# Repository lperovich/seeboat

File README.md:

# SeeBoat

Laura Perovich (perovich@media.mit.edu, Object-based Media, MIT Media Lab)

This project includes the code, hardware, and fabrication guides for SeeBoat, a community centered waterbody monitoring and data display platform. 

SeeBoat is a fleet of remote controlled boats that measure and display water quality in real time. It allows communities to explore water quality in their local lakes, rivers, and streams by changing the color of the boat in response to changes to the water quality. This data physicalization contextualizes the information and makes the water pollution data present in people's daily lives.

The boats measure water temperature, conductivity, and turbidity and display the data by real-time changes to the colors of the LEDs on the boat. Numeric sensor data is also transmitted via radio, visible through an Android app, and can be further recording using long exposure photos. SeeBoat makes environmental data experiential and interactive to help both communities and researchers better understand pollution and its implications.

The system is based on the Adafruit Feather M0 with RFM95 LoRa Radio (900MHz).

See "hardware" for a parts list, sensor schematics and board files, and 3D print files for sensors attachments.

See "software" for Arduino code for the entire system (main) and for each of the sensors (testing)

See "tutorials" for sensor fabrication guides and testing recommendations.

With technical contributions from Don Blair, Robert Henning, Sophia Struckman, Rod Bayliss, Rima Rebei, and Talia Spitz. Additional testing and assistance by ECO youth group (GreenRoots), Katherine Paseman, Claudia Chen, and Brian Mayton. 

Thanks to contributors Sara Wylie (Northeastern University) and Roseann Bongiovanni (GreenRoots). 

With funding and support from the Object Based Media (V. Michael Bove), the Media Lab Elements Fellows, and the Council for the Arts at MIT.

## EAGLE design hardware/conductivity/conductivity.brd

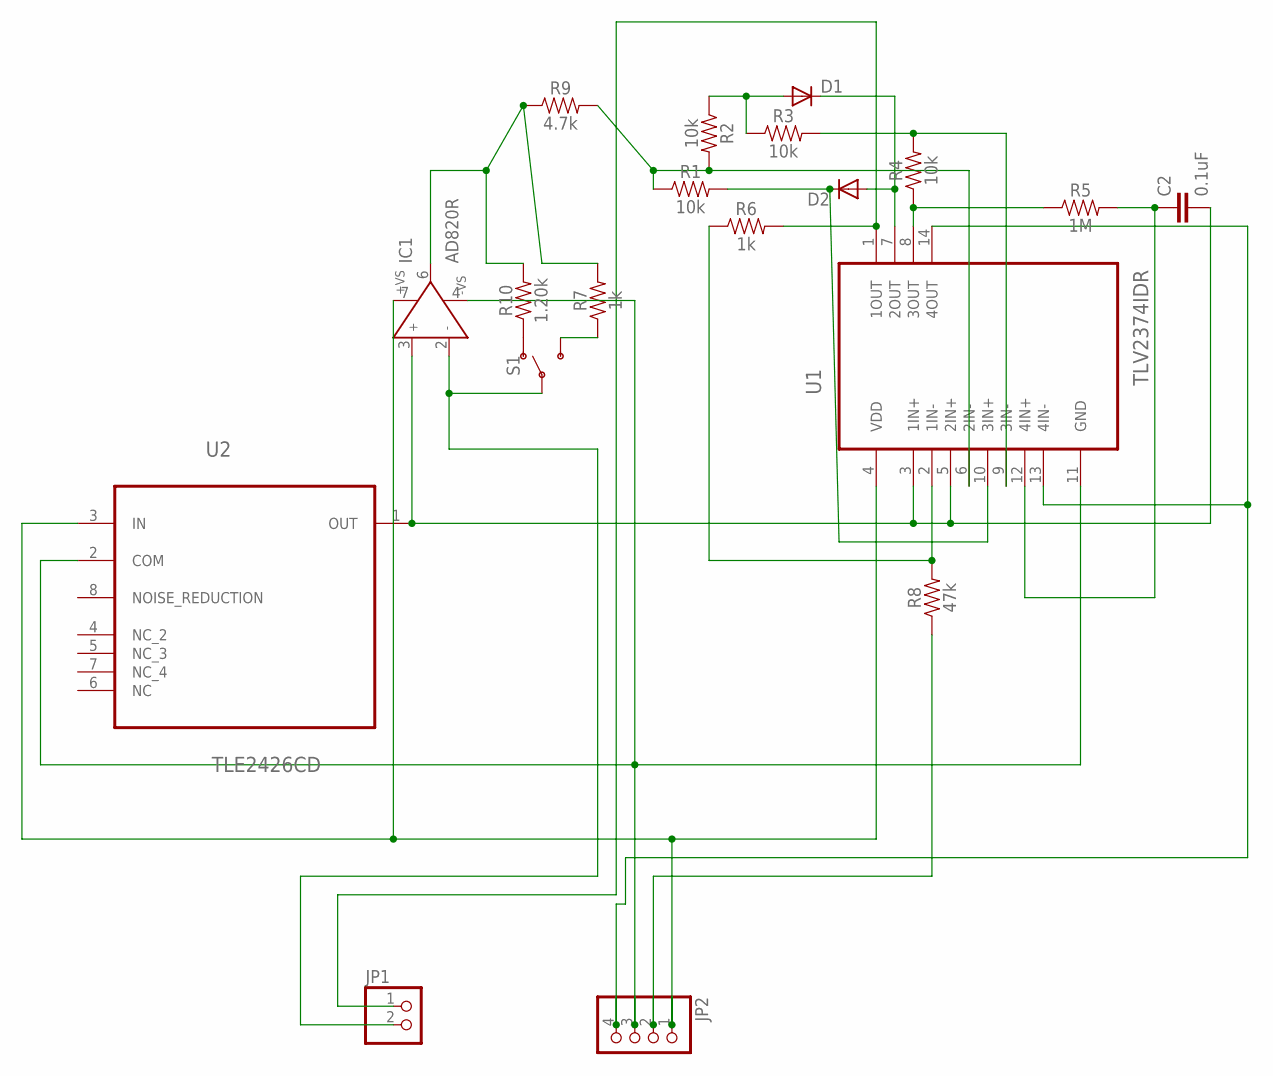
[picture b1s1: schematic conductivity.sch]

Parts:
C2: 0.1uF; 0603
D1, D2: DIODESOD123; SOD123
IC1: AD820R; SO8
JP1: PINHD-1X2; 1X02
JP2: PINHD-1X4; 1X04
R1, R2, R3, R4: 10k; 0603
R5: 1M; 0603
R6, R7: 1k; 0603
R8: 47k; 0603
R9: 4.7k; 0603
R10: 1.20k; 0603
S1: SWITCH-SPDT-SMD-AYZ0202; SWITCH_DPDT_SMD_AYZ0202
U1: TLV2374IDR; SOIC127P600X175-14N
U2: TLE2426CD; SOIC127P600X175-8N

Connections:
FROMWATER: IC1.2 (IN-), JP1.2, S1.2
unnamed: IC1.7 (+VS), JP2.1, U1.4 (VDD), U2.3 (IN)
unnamed: R10.1, S1.1 (O)
unnamed: C2.2, IC1.3 (IN+), U1.3 (1IN+), U1.5 (2IN+), U2.1 (OUT)
unnamed: R6.1, R8.2, U1.2 (1IN-)
unnamed: IC1.6 (OUT), R7.2, R9.1, R10.2
unnamed: R1.1, R2.2, R9.2, U1.6 (2IN-)
unnamed: D1.ANODE (A), R2.1, R3.1
unnamed: D1.CATHODE (C), D2.ANODE (A), U1.7 (2OUT)
unnamed: D2.CATHODE (C), R1.2, U1.10 (3IN+)
unnamed: R3.2, R4.2, U1.9 (3IN-)
unnamed: R4.1, R5.1, U1.8 (3OUT)
unnamed: C2.1, R5.2, U1.12 (4IN+)
unnamed: JP2.4, U1.13 (4IN-), U1.14 (4OUT)
unnamed: JP2.2, R8.1
unnamed: IC1.4 (-VS), JP2.3, U1.11 (GND), U2.2 (COM)
unnamed: JP1.1, R6.2, U1.1 (1OUT)
unnamed: R7.1, S1.3 (S)

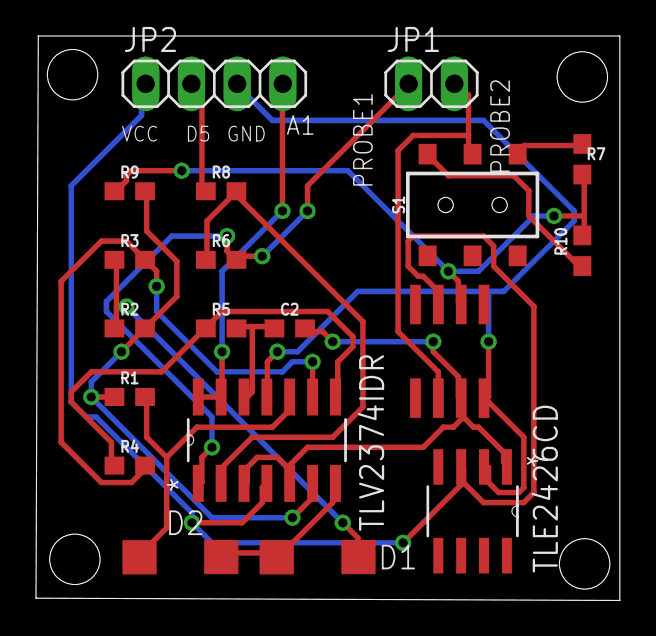
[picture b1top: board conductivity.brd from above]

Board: 2 copper layers, 32.4 x 31.4 mm, 19 parts (0 on the bottom side), 18 nets.

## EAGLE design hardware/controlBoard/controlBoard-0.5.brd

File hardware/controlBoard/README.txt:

Laura Perovich: SeeBoat control board for all the sensors 

--third board layer to be used with Featherwing ultimate GPS and Feather M0 LoRa
--see github parts list in hardware folder for parts details

######### Update 7/3/19
Fixed the labels on the LED strand connector

######### Update 6/23/18
Removed on board LED, spaced out the headers to better fit all the parts and the labels
Included DotStar LED strand connector
Water sensor to tell if it's in water is unnecessary, not implemented

######### Update 5/25/17
Combines the fishet-0.1 board with GPS to works as a breakout board for the feather M0 w/LoRa

parts from the fishnet to include:
*tricolor LED (3 pwm pins, other sides to ground)
*on/off switch for board
*temperature sensor connector (SDA, SCL, GND, PWR)
*turbidity sensor connector
*conductivity sensor connector
*water sensor (to tell if it's in water or not) [UNNECESSARY, NOT IMPLEMENTED]

GPS featherwing includes:
*GPS
*clock via GPS

#############################################
ORIGINAL BOARD LAYOUT:
# Adafruit-Ultimate-GPS-FeatherWing-PCB
PCB files for the Adafruit Ultimate GPS FeatherWing
Format is EagleCAD schematic and board layout
For more details, check out the product page at
   * https://www.adafruit.com/products/3133
Designed by Adafruit Industries.  
Creative Commons Attribution, Share-Alike license, check license.txt for more information
All text above must be included in any redistribution

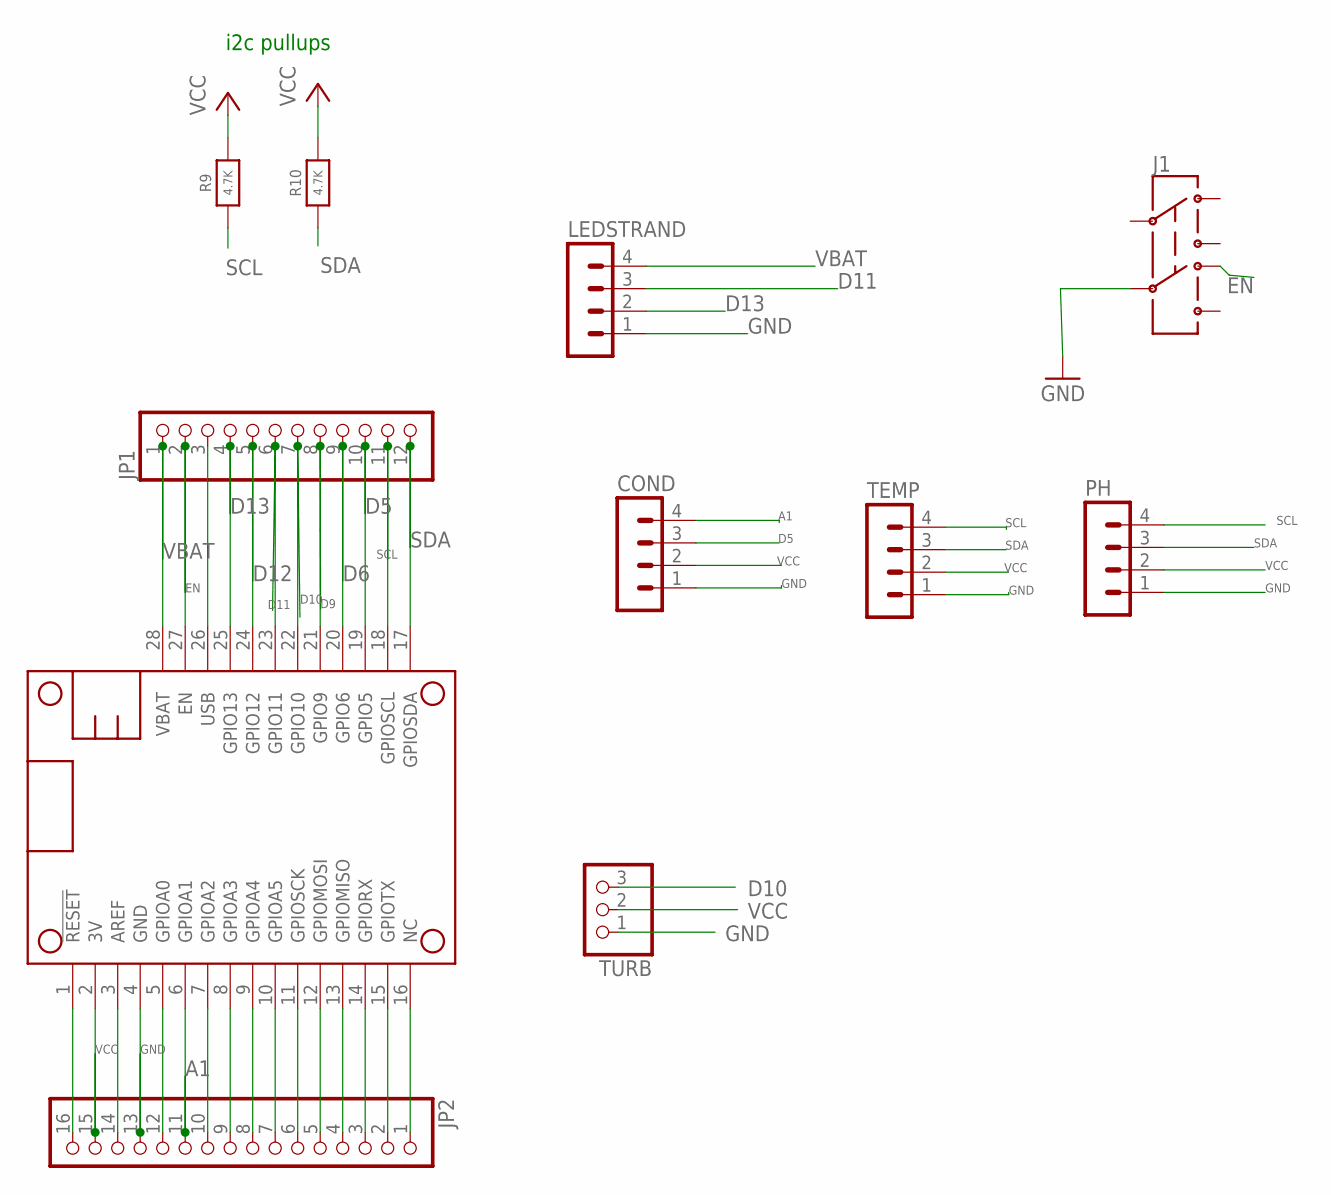
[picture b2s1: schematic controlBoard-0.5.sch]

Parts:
COND: MA04-1
J1: AYZ0202
JP1: PINHD-1X12; 1X12
JP2: PINHD-1X16; 1X16
LEDSTRAND: MA04-1
MS1: FEATHERWING
PH: MA04-1
R9, R10: 4.7K; 0603-NO
TEMP: MA04-1
TURB: PINHD-1X3; 1X03

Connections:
A1: COND.4, JP2.11, MS1.6 (GPIOA1)
D5: COND.3, JP1.10, MS1.19 (GPIO5)
D6: JP1.9, MS1.20 (GPIO6)
D9: JP1.8, MS1.21 (GPIO9)
D10: JP1.7, MS1.22 (GPIO10), TURB.3
D11: JP1.6, LEDSTRAND.3, MS1.23 (GPIO11)
D12: JP1.5, MS1.24 (GPIO12)
D13: JP1.4, LEDSTRAND.2, MS1.25 (GPIO13)
EN: J1.6 (4), JP1.2, MS1.27 (EN)
GND: COND.1, J1.5, JP2.13, LEDSTRAND.1, MS1.4 (GND), PH.1, TEMP.1, TURB.1
unnamed: JP2.1, MS1.16 (NC)
unnamed: JP2.2, MS1.15 (GPIOTX)
unnamed: JP2.3, MS1.14 (GPIORX)
unnamed: JP2.4, MS1.13 (GPIOMISO)
unnamed: JP2.5, MS1.12 (GPIOMOSI)
unnamed: JP2.6, MS1.11 (GPIOSCK)
unnamed: JP2.7, MS1.10 (GPIOA5)
unnamed: JP2.8, MS1.9 (GPIOA4)
unnamed: JP2.9, MS1.8 (GPIOA3)
unnamed: JP2.10, MS1.7 (GPIOA2)
unnamed: JP2.12, MS1.5 (GPIOA0)
unnamed: JP2.14, MS1.3 (AREF)
unnamed: JP2.16, MS1.1 (!RESET)
SCL: JP1.11, MS1.18 (GPIOSCL), PH.4, R9.1, TEMP.4
SDA: JP1.12, MS1.17 (GPIOSDA), PH.3, R10.1, TEMP.3
USB: JP1.3, MS1.26 (USB)
VBAT: JP1.1, LEDSTRAND.4, MS1.28 (VBAT)
VCC: COND.2, JP2.15, MS1.2 (3V), PH.2, R9.2, R10.2, TEMP.2, TURB.2

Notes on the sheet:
i2c pullups

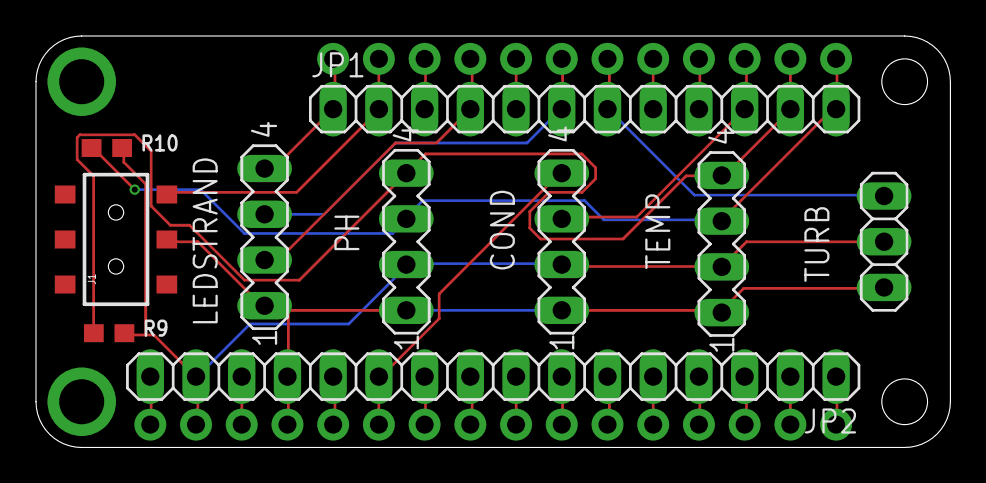
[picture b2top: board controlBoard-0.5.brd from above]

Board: 2 copper layers, 50.8 x 22.9 mm, 11 parts (0 on the bottom side), 28 nets.

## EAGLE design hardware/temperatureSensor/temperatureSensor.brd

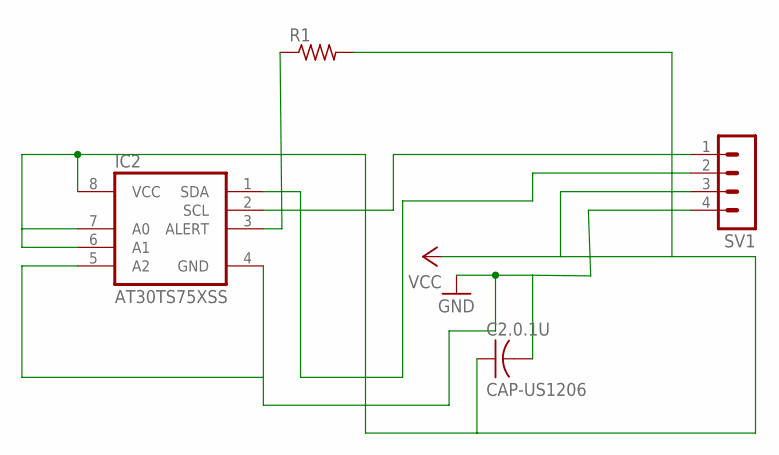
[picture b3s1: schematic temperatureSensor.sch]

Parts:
C2.0.1U: CAP-US1206; C1206
IC2: AT30TS75XSS; SO8
R1: RES-US1206; R1206
SV1: MA04-1

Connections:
D2: IC2.3 (ALERT), R1.1
GND: C2.0.1U.2, IC2.4 (GND), IC2.5 (A2), SV1.4
unnamed: IC2.2 (SCL), SV1.1
SDA: IC2.1 (SDA), SV1.2
VCC: C2.0.1U.1, IC2.6 (A1), IC2.7 (A0), IC2.8 (VCC), R1.2, SV1.3

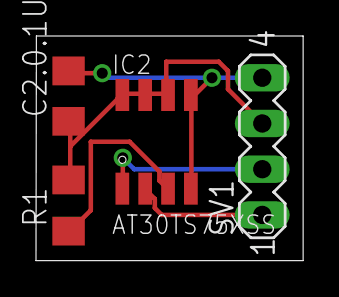
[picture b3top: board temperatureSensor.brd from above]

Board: 2 copper layers, 14.8 x 12.5 mm, 4 parts (0 on the bottom side), 5 nets.

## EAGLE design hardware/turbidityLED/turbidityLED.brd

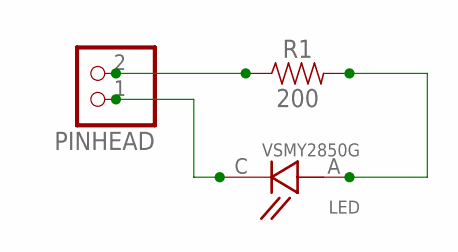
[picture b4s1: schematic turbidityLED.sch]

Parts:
LED: VSMY2850G; SOD4223X279N
PINHEAD: PINHD-1X2; 1X02
R1: 200; 0603

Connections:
unnamed: PINHEAD.2, R1.1
unnamed: LED.A, R1.2
unnamed: LED.C, PINHEAD.1

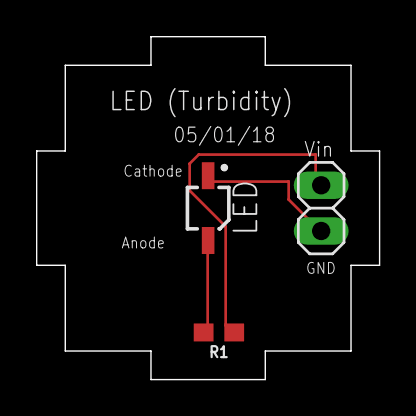
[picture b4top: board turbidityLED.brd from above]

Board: 2 copper layers, 19.1 x 19.1 mm, 3 parts (0 on the bottom side), 3 nets.

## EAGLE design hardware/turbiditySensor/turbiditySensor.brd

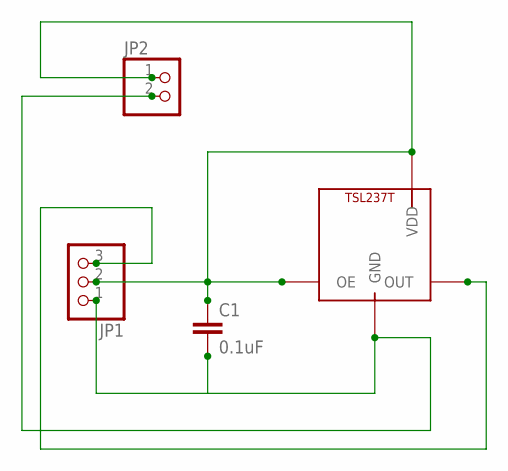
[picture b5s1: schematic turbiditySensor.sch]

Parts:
C1: 0.1uF; 0603
JP1: PINHD-1X3; 1X03
JP2: PINHD-1X2; 1X02
SENSOR: WS2812B3535; LED3535

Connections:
unnamed: JP1.3, SENSOR.4 (OUT)
unnamed: C1.1, JP1.2, JP2.1, SENSOR.1 (OE), SENSOR.3 (VDD)
unnamed: C1.2, JP1.1, JP2.2, SENSOR.2 (GND)

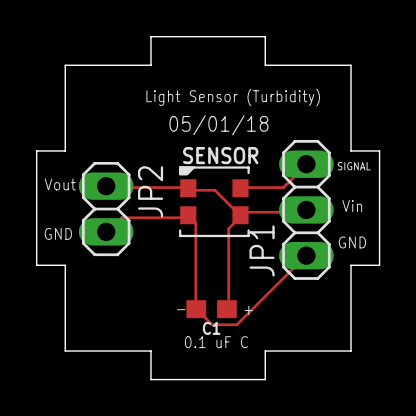
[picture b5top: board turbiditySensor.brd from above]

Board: 2 copper layers, 19.1 x 19.1 mm, 4 parts (0 on the bottom side), 3 nets.

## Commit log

2017-01-25 Create stuff
2017-01-25 Create blah
2017-01-25 Rename fishnetLEDtest/fishnetLEDtest.ino to software/fishnetLEDtest/fishnetLEDtest.ino
2018-06-25 Rename hardware/fishnet-0.1/fishnet-0.1.bom to hardware/archive/fishnet-0.1/fishnet-0.1.bom
2018-06-25 Rename hardware/fishnet-0.1/fishnet-0.1.brd to hardware/archive/fishnet-0.1/fishnet-0.1.brd
2018-06-25 Rename hardware/fishnet-0.1/eagle.epf to hardware/archive/fishnet-0.1/eagle.epf
2018-06-25 Rename hardware/fishnet-0.1/fishnet-0.1.pro to hardware/archive/fishnet-0.1/fishnet-0.1.pro
2018-06-25 Rename hardware/fishnet-0.1/fishnet-0.1.sch to hardware/archive/fishnet-0.1/fishnet-0.1.sch
2018-06-25 Rename hardware/fishnet-0.1/fishnet-0.1_details.bom to hardware/archive/fishnet-0.1/fishnet-0.1_details.bom
2018-06-25 Rename hardware/riffle-0.96-breakout-0.71-AT30TS750A_SmallOneHeadersI2C/eagle.epf to hardware/archive/riffle-0.96-breakout-0.71-AT30TS750A_SmallOneHeadersI2C/eagle.epf
2018-06-25 Rename hardware/riffle-0.96-breakout-0.71-AT30TS750A_SmallOneHeadersI2C/riffle-CTL-0.2-blank.brd to hardware/archive/riffle-0.96-breakout-0.71-AT30TS750A_SmallOneHeadersI2C/riffle-CTL-0.2-blank.brd
2018-06-25 major update June 2018
2018-06-25 major project update june 2018
2018-06-25 board and parts list update june 2018
2018-06-25 robert code
2018-06-26 control board update
2018-06-27 hardware update
2018-07-09 app source file fix
2018-07-11 This is a test commit!
2018-07-11 This is my first commit message.
2018-07-11 I committed a smiley face somewhere...
2018-07-11 This is the first commit!
2018-07-19 This is first commit
2018-07-24 update parts lists w/header
2019-03-01 Update conductivity.ino
    conductivity now outputs voltage as a float, not an int
2019-05-03 Updated main code to current LED strip + sensors.
2019-05-03 Revert "Updated main code to current LED strip + sensors."
    This reverts commit e346d15b47c64aa68b4e26eb6b5f228a005aae59.
2019-05-03 2nd try: Updated main code to current LED strip + sensors.""
2019-05-03 parts list
2019-05-10 Integrated all sensor code.
2019-06-12 updated parts list and adding tutorials
2019-06-12 parts list diode update
2019-06-13 parts list and boards update
2019-06-21 parts list update with new attachers and conductivity code fix
2019-06-21 add temperature tutorial
2019-06-21 description update
2019-07-03 fixed labels on LED strand on control board, added 3D print parts
2019-07-03 update pH and LED testing code
2019-07-05 update conductivity headers, add 3D print parts and laser cut parts
2019-07-08 Made easier to change sensor variables, updated tutorials.
2019-07-09 Added control board tutorial.
2019-07-09 shorten light panels for boat, add LED holders, re-label turbidity fil
2019-07-09 add tubing conductivity holder, update boat parts
2019-07-11 Added LED tutorial.
2019-07-11 add template for cutting out conductivity probe holder
2019-07-16 Added turbidity calibration tutorial, updated sensor integration tutorial, added leakTesting LED code.
2019-07-17 added setting strip to one color
2019-07-17 add LED strand fade testing code
2019-07-17 more LED code updates
2019-07-19 Updated tutroials with turbidity changes and photos of boat process.
2019-07-19 Added pH documentation.
2019-07-23 Updated main code to adjust calibration per boat, updated tutorials.
2019-07-25 Add GPS delay to main code.
2019-07-30 Added pH o-rings to parts list.
2019-07-30 python code for getting csvs
2019-07-31 Added csv python code for windows.
2019-07-31 test python plotting code
2019-07-31 more python plotting
2019-08-01 all sensor python plots, windows and linux
2019-08-02 updated sensor tutorials with wire lengths/diagrams.
2019-08-05 Added 2nd boat calibration code.
2019-08-05 Added boatName to Rx, Tx code, updated headers in CSV code.
2019-08-09 more points in python code
2019-08-12 Zeroed conductivity so it shouldn't output any negative conductivities when the voltage = 0.
2019-08-15 mutligraph python code
2019-08-20 deleted misc file
2019-08-20 fixed turbidity lights code
2019-08-20 fixed pH demical+LED colors
2019-08-20 Revert "fixed pH demical+LED colors"
    This reverts commit 18743cfefc8759074a153865a1ace62f1e04c31f.
2019-08-20 updated pH decimals
2019-08-23 Updated boat-making tutorials.
2019-08-23 got rid of zeroing conductivity
2019-09-25 added GPS data logging code and info on the code files
2019-09-26 fix decimals, date, and file names in GPS code
2019-09-27 Added shark.
2019-10-03 GPS data
2019-10-04 windows graph fixes
2019-10-06 add shark to Rx code
2019-11-16 Added frequency sweep.
2019-11-22 november update
2019-11-22 november update 2
2019-11-22 Revert "Updating."
2019-11-24 Updating cond SD file, freqSweep to include average.
2019-11-24 Unsure what these updates are.
2019-12-13 Added averaging.
2019-12-13 analog decimals adding hopefully
2019-12-13 Trying to fix.
2019-12-13 More
2019-12-13 getting rid of file
2019-12-13 Adding cond back.
2019-12-13 adding 12-bit to conductivity testing files
2020-02-05 adding conductivity sine wave code
2020-02-26 modified conductivity sine wave code DB
2020-11-12 sine code nov 2020 calibration

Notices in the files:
parts and their libraries:
SparkFun-Capacitors: Licensing: Creative Commons ShareAlike 4.0 International - https://creativecommons.org/licenses/by-sa/4.0
